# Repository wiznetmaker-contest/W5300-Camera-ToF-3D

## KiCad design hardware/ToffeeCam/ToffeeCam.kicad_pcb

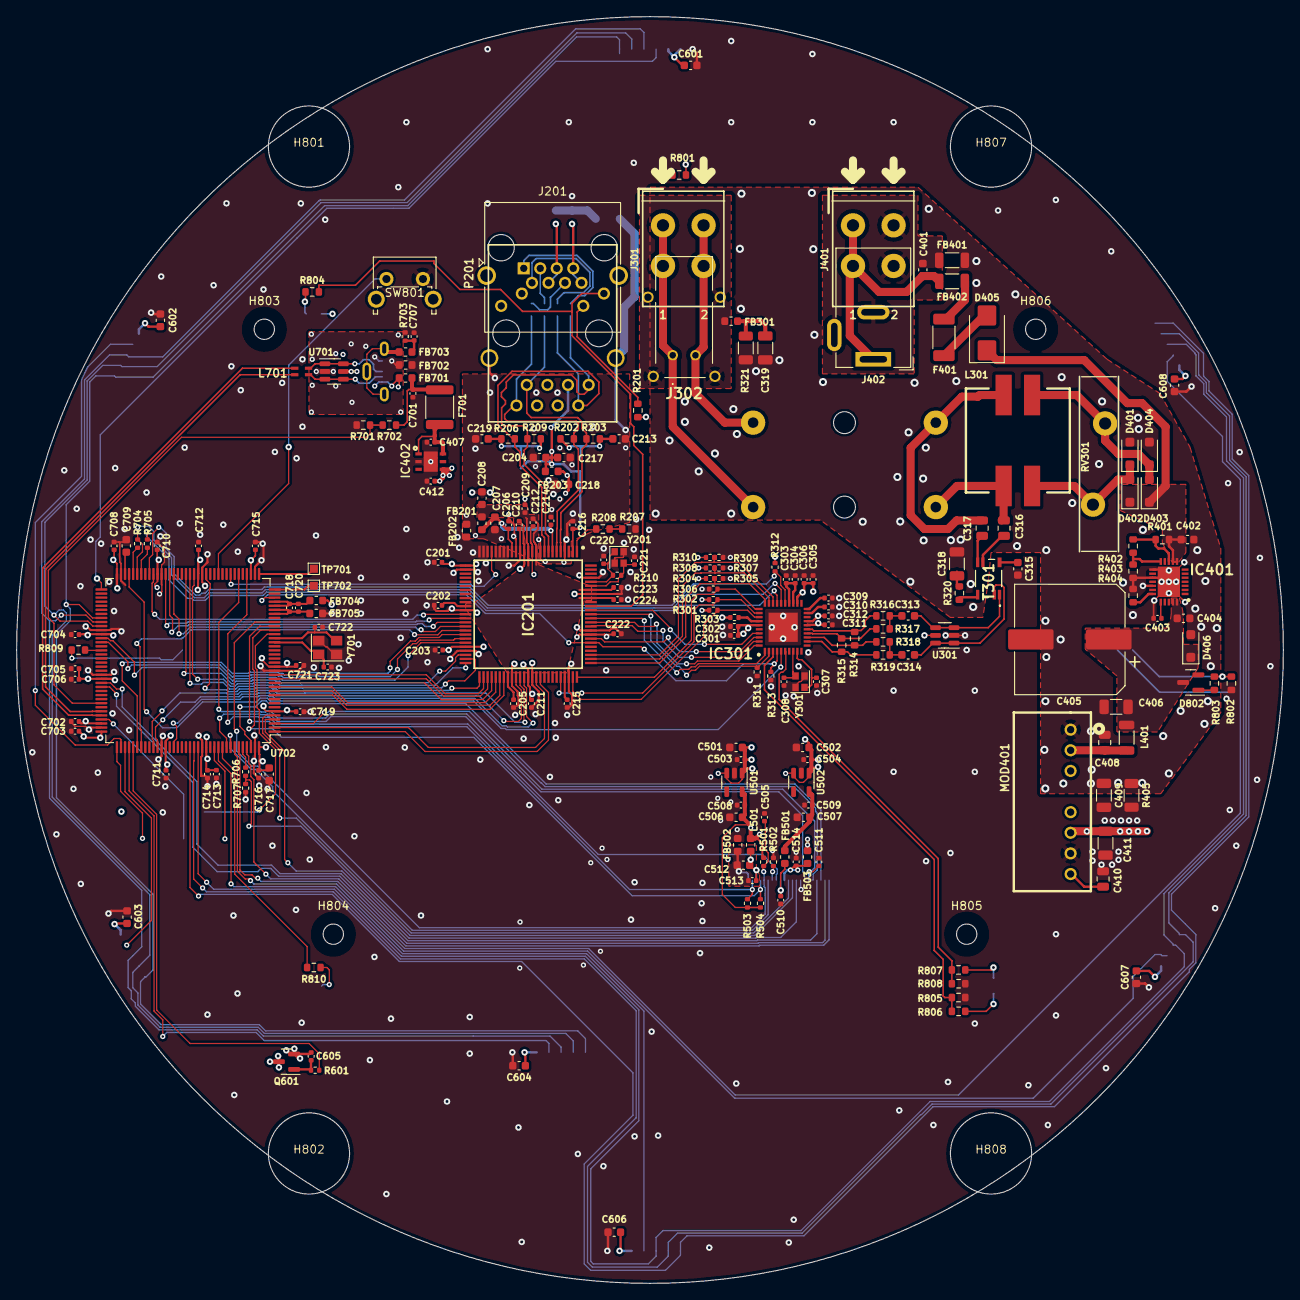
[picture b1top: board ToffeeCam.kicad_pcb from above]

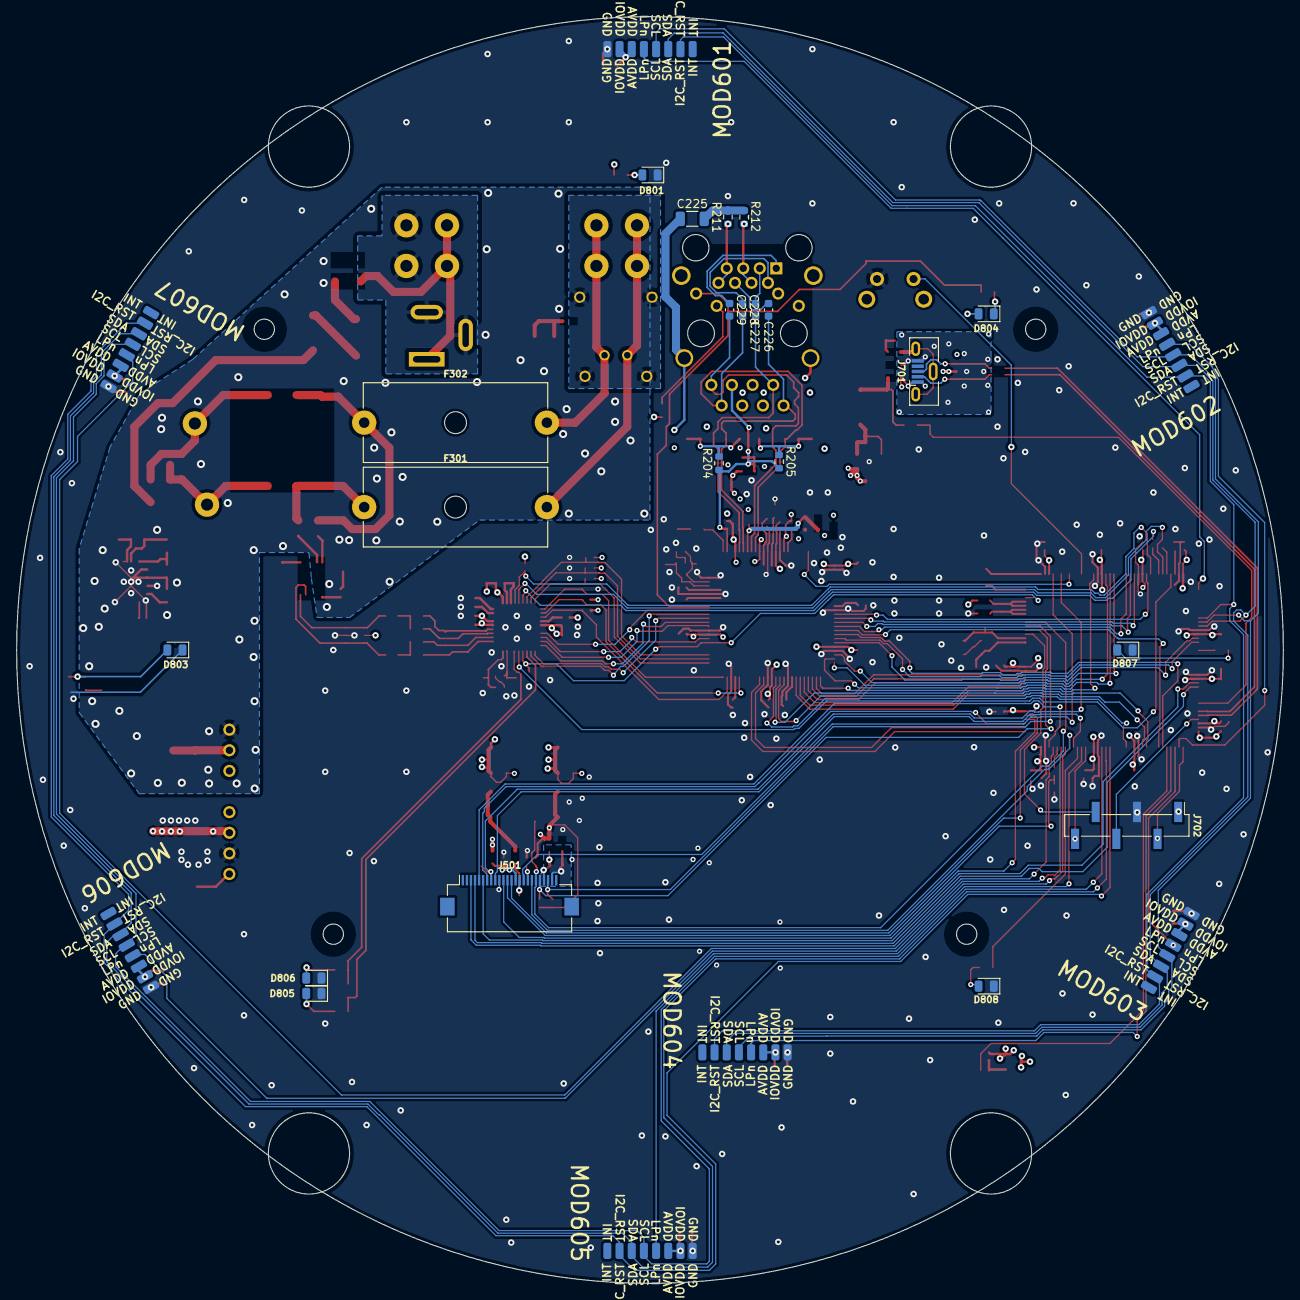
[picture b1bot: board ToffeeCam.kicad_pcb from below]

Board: 4 copper layers, 156.0 x 156.0 mm, 244 parts (28 on the bottom side), 182 nets.

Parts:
C201, C202, C203, C205, C206, C210, C211, C212, C214, C215, C216, C222, C223, C224, C302, C303, C306, C310, C312, C503, C504, C505, C508, C509, C510, C513, C514, C701, C702, C703, C704, C705, C708, C710, C711, C712, C713, C715, C716, C718, C719, C721: 100n; C_0402_1005Metric
C204, C213, C219, C315, C401, C402, C404: 100n; C_0603_1608Metric
C207, C208, C217, C218, C501, C502, C506, C507, C512, C601, C602, C603, C604, C606, C607, C608, C717: 10u; C_0603_1608Metric
C209, C403, C706, C714: 2u2; C_0402_1005Metric
C220, C221: 13p; C_0402_1005Metric
C225, C318, C319, C409: 1n_2kV; C_1206_3216Metric
C226, C227, C228, C229: 33n; C_0603_1608Metric
C301, C305, C311: 10n; C_0402_1005Metric
C304: 680n; C_0402_1005Metric
C307, C308: 16p; C_0402_1005Metric
C309, C407, C412, C605, C720: 1u; C_0402_1005Metric
C313, C314: 220n; C_0603_1608Metric
C316, C317, C408: 1u; C_0805_2012Metric
C405: 330u_50V; CP_Elec_12,5x13.5
C406: 10u; C_1206_3216Metric
C410: 10u; C_0805_2012Metric
C411: 100u; C_1206_3216Metric
C511: 22p; C_0402_1005Metric
C707: 1n; C_0402_1005Metric
C709: 4u7; C_0603_1608Metric
C722, C723: 6p8; C_0402_1005Metric
D401, D402, D403, D404, D406: PMEG6010CEH; D_SOD-123F
D405: SK56; D_SMB
D801, D803, D804, D805, D806, D807, D808: LED; LED_0805_2012Metric
D802: BZX84Cxx; SOT-23
F301, F302: Fuse; Fuseholder_Cylinder-5x20mm_Schurter_0031_8201_Horizontal_Op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
F401: Polyfuse; Fuse_2010_5025Metric
F701: Polyfuse_Small; Fuse_1812_4532Metric
FB201, FB202, FB203, FB301, FB501, FB502, FB503, FB701, FB702, FB703: HH-1M1608-121JT; FB_0603_1608Metric
FB401, FB402: WE-742792122; FB_1206_3216Metric
FB704, FB705: HH-1M1608-221JT; FB_0603_1608Metric
H801, H802, H807, H808: MountingHole; MountingHole-10mm
H803, H804, H805, H806: MountingHole; MountingHole_2.5mm
IC201: W5300; QFP50P1600X1600X160-100N
IC301: ADIN1100BCPZ; ADIN1100
IC401: TPS26400RHFR; QFN50P400X500X100-25N-D
IC402: LDL112PV33R; SON95P300X300X100-7N-D
J201: RJ45; RJ45_Amphenol_RJHSE5380
J301, J401: Messtechnik_AK3001/2-KD-5,0; Messtechnik_AK3001_2-KD-5.0
J302: 09452812800
J402: Wuerth-694108301002; BarrelJack_Wuerth_6941xx301002
J501: Hirose_FH12-24S-0.5SH(55); Hirose_FH12-24S-0.5SH_1x24-1MP_P0.50mm_Horizontal
J701: USB_B_Micro; USB_Micro-B_Molex-105133-0001
J702: Conn_01x06; PinHeader_1x06_P2.54mm_Vertical_SMD_Pin1Left
L301: 100u; 744871101
L401: 470n; L_1206_3216Metric
L501: 3u3; FB_0603_1608Metric
L701: 744233121; WE-CNSW_08059
MOD401: AM3G-2403S-NZ; AM3G-NZ
MOD601, MOD602, MOD603, MOD604, MOD605, MOD606, MOD607: VL53L7CX-SATEL; VL53L5CX-SATEL
P201: RB1-125BAG1A; WIZNET_RB1-125BAG1A
Q601: AO3401A; SOT-23
R201, R207: 330; R_0603_1608Metric
R202, R203, R206, R209, R316, R319: 49R9; R_0603_1608Metric
R204, R205: 0R; R_0603_1608Metric
R208: 12k_1%; R_0603_1608Metric
R210, R703: 1M; R_0402_1005Metric
R211, R212: 75R; R_0603_1608Metric
R301, R302, R303, R304, R305, R306, R307, R308, R309, R310, R311, R313, R503, R504: 4k7; R_0402_1005Metric
R312: 1k5; R_0402_1005Metric
R314, R315: 10k2; R_0603_1608Metric
R317, R318: 5k1; R_0603_1608Metric
R320, R806, R807: 100; R_0603_1608Metric
R321, R405: 1M; R_1206_3216Metric
R401: 237k; R_0603_1608Metric
R402: 6k8; R_0603_1608Metric
R403: 10k; R_0603_1608Metric
R404: 53k6; R_0603_1608Metric
R501, R502, R601: 10k; R_0402_1005Metric
R701: 47k; R_0603_1608Metric
R702: 22k; R_0603_1608Metric
R704, R705: 22R; R_0402_1005Metric
R706: 49R9; R_0402_1005Metric
R707: 330R; R_0402_1005Metric
R801, R804, R809, R810: 330R; R_0603_1608Metric
R802, R803, R805, R808: 4k7; R_0603_1608Metric
RV301: S20K30; RV_Disc_D21.5mm_W4.3mm_P10mm
SW801: SW_Push; SW_Tactile_SPST_Angled_PTS645Vx83-2LFS
T301: 74930000
TP701, TP702: TestPoint; TestPoint_Pad_1.0x1.0mm
U301, U701: WE-TVS-82400102; SOT-23-6
U501: TLV74328PDBVR; SOT-23-5
U502: TLV75512PDBVR; SOT-23-5
U702: STM32U575ZITx; LQFP-144_20x20mm_P0.5mm
Y201, Y301: 7R-25.000MAAQ; Crystal_SMD_2016-4Pin_2.0x1.6mm
Y701: ABM8G-16.000MHZ-4Y-T3; Crystal_SMD_Abracon_ABM8G-4Pin_3.2x2.5mm

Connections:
2V8A: C512.2, C513.2, J501.21, L501.2
2V8D: C506.2, C508.2, FB503.1, L501.1, R501.2, R503.1, R504.1, U501.5 (OUT)
+1V2: C507.2, C509.2, FB501.2, U502.5 (OUT)
+1V8A: C206.2, C207.1, C214.2, FB201.2, IC201.7 (VCC1A8_1), IC201.17 (VCC1A8_2)
+1V8D: C202.2, C205.1, C208.1, C209.1, C212.2, C215.1, C223.1, C224.1, FB201.1, IC201.11 (VCC1V8_1), IC201.13 (1V8O), IC201.36 (VCC1V8_2), IC201.58 (VCC1V8_3), IC201.72 (VCC1V8_4), IC201.92 (VCC1V8_5), IC201.94 (VCC1V8_6)
+3.3VP: C601.1, C602.1, C603.1, C604.1, C606.1, C607.1, C608.1, MOD601.6 (AVDD), MOD601.7 (IOVDD), MOD602.6 (AVDD), MOD602.7 (IOVDD), MOD603.6 (AVDD), MOD603.7 (IOVDD), MOD604.6 (AVDD), MOD604.7 (IOVDD), MOD605.6 (AVDD), MOD605.7 (IOVDD), MOD606.6 (AVDD), MOD606.7 (IOVDD), MOD607.6 (AVDD), MOD607.7 (IOVDD), Q601.3 (D)
+3V3: C201.2, C203.2, C210.2, C211.1, C218.1, C222.1, C301.1, C302.2, C305.1, C306.1, C311.1, C312.1, C411.1, C412.1, C501.2, C502.2, C503.2, C504.2, C605.2, C702.2, C703.2, C704.2, C705.2, C706.2, C708.2, C710.2, C711.2, C712.2, C713.2, C714.2, C715.2, C716.2, C717.2, C719.2, C721.2, D804.2 (A), FB203.1, FB704.2, IC201.14 (VCC3V3_1), IC201.26 (VCC3V3_2), IC201.46 (VCC3V3_3), IC201.63 (VCC3V3_4), IC201.83 (VCC3V3_5), IC301.16 (AVDD_H_1), IC301.17 (AVDD_H_2), IC301.22 (AVDD_L), IC301.35 (VDDIO), IC402.4 (VOUT), J702.1, MOD401.6 (+Vout), Q601.2 (S), R201.2, R301.1, R302.1, R303.1, R304.1, R308.1, R310.1, R312.2, R801.2, U301.5, U501.1 (IN), U501.3 (EN), U502.1 (IN), U502.3 (EN), U702.6 (VBAT), U702.17 (VDD), U702.39 (VDD), U702.52 (VDD), U702.62 (VDD), U702.72 (VDD), U702.84 (VDD), U702.95 (VDDIO2), U702.106 (VDDUSB), U702.108 (VDD), U702.121 (VDD), U702.131 (VDDIO2), U702.144 (VDD)
+3V3A: C204.1, C216.2, C217.1, FB203.2, IC201.2 (VCC3A3), P201.R3 (CT), R204.1, R205.2
+5V-USB: C407.1, F701.2, IC402.1 (EN), IC402.6 (VIN)
/Camera/CAM-PWDN: J501.17, R502.2
/MCU/CAMXCLK: R706.2, U702.140 (PB9)
/MCU/SWCLK: J702.2, U702.109 (PA14)
/MCU/SWDIO: J702.4, U702.105 (PA13)
/MCU/SWO: J702.6, U702.133 (PB3)
/MCU/USB-5V: FB701.1, J701.1 (VBUS), U701.5
/MCU/USB-DN: L701.2, U702.103 (PA11)
/MCU/USB-DP: L701.3 (4), U702.104 (PA12)
/MCU/USB-GND: FB702.2, J701.5 (GND), U701.2
/MCU/USB-VBUS-DETECT: R701.1, R702.2, U702.101 (PA9)
/MCU/VBUS: C701.1, F701.1, FB701.2, R702.1
/MCU/nRST: J702.5, U702.25 (NRST)
/PowerSupply/CONV_IN: C408.1, L401.2, MOD401.2 (+Vin)
/PowerSupply/PROTECT-IN: C402.1, D402.1 (K), D403.1 (K), D405.1 (K), IC401.8 (IN), R401.1
/PowerSupply/SUPP_M: C401.2, FB401.1, J401.2, J402.2, J402.3
/PowerSupply/SUPP_P: C401.1, FB402.2, J401.1, J402.1
/Wiznet-W5300/RXIN: C226.2, IC201.6 (RXIN), P201.R8 (RD-), R202.1
/Wiznet-W5300/RXIP: C227.2, IC201.5 (RXIP), P201.R7 (RD+), R203.1
/Wiznet-W5300/TXON: C228.2, IC201.9 (TXON), P201.R2 (TD-), R206.2
/Wiznet-W5300/TXOP: C229.2, IC201.8 (TXOP), P201.R1 (TD+), R209.2
CAM-D0: J501.6, U702.96 (PC6)
CAM-D1: J501.4, U702.97 (PC7)
CAM-D2: J501.3, U702.141 (PE0)
CAM-D3: J501.5, U702.142 (PE1)
CAM-D4: J501.7, U702.3 (PE4)
CAM-D5: J501.9, U702.136 (PB6)
CAM-D6: J501.11, U702.4 (PE5)
CAM-D7: J501.13, U702.5 (PE6)
CAM-HSYNC: J501.16, U702.40 (PA4)
CAM-PCLK: C511.2, J501.8, U702.42 (PA6)
CAM-SCL: J501.20, R504.2, U702.26 (PC0)
CAM-SDA: J501.22, R503.2, U702.27 (PC1)
CAM-VSYNC: J501.18, U702.137 (PB7)
CAM-XCLK: J501.12, R706.1, R707.1
CAM-nRESET: C505.1, J501.19, R501.1, U702.28 (PC2)
CAMGNDA: C512.1, C513.1, FB502.1, J501.23
ETH-BUS-ADDR0: IC201.57 (ADDR0), U702.10 (PF0)
ETH-BUS-ADDR1: IC201.56 (ADDR1), U702.11 (PF1)
ETH-BUS-ADDR2: IC201.55 (ADDR2), U702.12 (PF2)
ETH-BUS-ADDR3: IC201.54 (ADDR3), U702.13 (PF3)
ETH-BUS-ADDR4: IC201.53 (ADDR4), U702.14 (PF4)
ETH-BUS-ADDR5: IC201.52 (ADDR5), U702.15 (PF5)
ETH-BUS-ADDR6: IC201.51 (ADDR6), U702.50 (PF12)
ETH-BUS-ADDR7: IC201.50 (ADDR7), U702.53 (PF13)
ETH-BUS-ADDR8: IC201.49 (ADDR8), U702.54 (PF14)
ETH-BUS-ADDR9: IC201.48 (ADDR9), U702.55 (PF15)
ETH-BUS-DATA0: IC201.45 (DATA0), U702.85 (PD14)
ETH-BUS-DATA1: IC201.44 (DATA1), U702.86 (PD15)
ETH-BUS-DATA2: IC201.43 (DATA2), U702.114 (PD0)
ETH-BUS-DATA3: IC201.42 (DATA3), U702.115 (PD1)
ETH-BUS-DATA4: IC201.41 (DATA4), U702.58 (PE7)
ETH-BUS-DATA5: IC201.40 (DATA5), U702.59 (PE8)
ETH-BUS-DATA6: IC201.39 (DATA6), U702.60 (PE9)
ETH-BUS-DATA7: IC201.38 (DATA7), U702.63 (PE10)
ETH-BUS-nCS: IC201.62 (/CS), U702.123 (PD7)
ETH-BUS-nINT: IC201.65 (/INT), U702.2 (PE3)
ETH-BUS-nRD: IC201.61 (/RD), U702.118 (PD4)
ETH-BUS-nRESET: IC201.66 (/RESET), U702.1 (PE2)
ETH-BUS-nWR: IC201.60 (/WR), U702.119 (PD5)
ETH-LINKLED: IC201.90 (LINKLED), P201.L4, R804.2
ETH-MEDIA_SEL: IC201.22 (TEST_MODE0), U702.44 (PC4)
ETHGNDA: C204.2, C206.1, C207.2, C213.2, C214.1, C216.1, C217.2, C219.2, C225.1, FB202.2, IC201.4 (GNDA_1), IC201.10 (GNDA_2), IC201.16 (GNDA_3), P201.S1, P201.S2
GND: C201.1, C202.1, C203.1, C205.2, C208.2, C209.2, C210.1, C211.2, C212.1, C215.2, C218.2, C220.2, C221.1, C222.2, C223.2, C224.2, C301.2, C302.1, C303.2, C304.2, C305.2, C306.2, C307.2, C308.1, C309.2, C310.2, C311.2, C312.2, C315.1, C407.2, C409.2, C410.2, C411.2, C412.2, C501.1, C502.1, C503.1, C504.1, C505.2, C506.1, C507.1, C508.1, C509.1, C510.1, C511.1, C514.2, C601.2, C602.2, C603.2, C604.2, C606.2, C607.2, C608.2, C701.2, C702.1, C703.1, C704.1, C705.1, C706.1, C707.2, C708.1, C709.1, C710.1, C711.1, C712.1, C713.1, C714.1, C715.1, C716.1, C717.1, C719.1, C721.1, C722.2, C723.1, D801.1 (K), D803.1 (K), D805.1 (K), D806.1 (K), D807.1 (K), D808.1 (K), FB202.1, FB502.2, FB702.1, FB705.2, IC201.12 (GND_1), IC201.15 (GND_2), IC201.18 (BIT16EN), IC201.19 (TEST_MODE3), IC201.20 (TEST_MODE2), IC201.21 (TEST_MODE1), IC201.23 (OP_MODE0_1), IC201.24 (OP_MODE0_2), IC201.25 (OP_MODE2), IC201.27 (GND_3), IC201.37 (GND_4), IC201.47 (GND_5), IC201.59 (GND_6), IC201.64 (GND_7), IC201.73 (GND_8), IC201.84 (GND_9), IC201.93 (GND_10), IC201.97 (GND_11), IC301.41 (GND), IC402.2 (GND), IC402.7 (EP), J501.10, J702.3, MOD401.7 (-Vout), MOD601.8 (GND), MOD602.8 (GND), MOD603.8 (GND), MOD604.8 (GND), MOD605.8 (GND), MOD606.8 (GND), MOD607.8 (GND), R207.1, R305.1, R306.1, R307.1, R309.1, R311.1, R313.1, R405.2, R502.1, R701.2, R703.2, R707.2, R802.1, R805.2, R808.2, SW801.2, U301.2, U501.2 (GND), U502.2 (GND), U702.16 (VSS), U702.38 (VSS), U702.51 (VSS), U702.61 (VSS), U702.71 (VSS), U702.83 (VSS), U702.94 (VSS), U702.107 (VSS), U702.120 (VSS), U702.130 (VSS), U702.143 (VSS), Y201.2, Y201.4, Y301.2, Y301.4, Y701.2, Y701.4
GNDPWR: C318.2, C319.2, C402.2, C403.2, C404.2, C405.2, C406.2, C408.2, C409.1, D401.2 (A), D404.2 (A), D406.2 (A), FB401.2, IC401.13 (MODE), IC401.15 (RTN), IC401.17 (GND), IC401.25 (EP), MOD401.1 (-Vin), R321.2, R403.2, R404.2, R405.1
MCU-STATUS-1: R809.2, U702.88 (PG3)
MCU-STATUS-2: R810.2, U702.135 (PB5)
MII-CRS: IC201.81 (MII_CRS), IC301.4 (LINK_ST/PHYAD_2), R313.2, U702.34 (PA0)
MII-RXCLK: IC201.71 (MII_RXC), IC301.32 (MACIF_SEL0/RX_CLK), R302.2
MII-RXD0: IC201.75 (MII_RXD0), IC301.31 (~TX2P4_EN/RXD_0), R306.2
MII-RXD1: IC201.76 (MII_RXD1), IC301.30 (MS_SEL/RXD_1), R304.2, R305.2
MII-RXD2: IC201.77 (MII_RXD2), IC301.29 (PHYAD_0/RXD_2), R307.2, R308.2
MII-RXD3: IC201.78 (MII_RXD3), IC301.28 (PHYAD_1/RXD_3), R309.2, R310.2
MII-RXDV: IC201.74 (MII_RXDV), IC301.33 (~SWPD_EN/RX_DV), R301.2
MII-TXCLK: IC201.82 (MII_TXC), IC301.38 (TX_CLK)
MII-TXD0: IC201.85 (/SPDLED(MII_TXD0)), IC301.39 (TXD_0)
MII-TXD1: IC201.86 (/FDXLED(MII_TXD1)), IC301.40 (TXD_1)
MII-TXD2: IC201.87 (/COLLED(MLL_TXD2)), IC301.1 (TXD_2)
MII-TXD3: IC201.88 (/RXLED(MII_TXD3)), IC301.2 (TXD_3/MEDIA_CNV), R311.2
MII-TXEN: IC201.89 (/TXLED(MII_TXEN)), IC301.37 (TX_EN)
unnamed: C213.1, R202.2, R203.2, R204.2
unnamed: C219.1, R205.1, R206.1, R209.1
unnamed: C225.2, R211.2, R212.2
unnamed: C226.1, J201.6
unnamed: C227.1, J201.3
unnamed: C228.1, J201.2
unnamed: C229.1, J201.1
unnamed: C313.2, R316.2, R317.2
unnamed: C314.1, R318.2, R319.2
unnamed: C316.2, F301.1, L301.4
unnamed: C317.2, F302.1, L301.1
unnamed: C318.1, R320.2
unnamed: C319.1, FB301.2, R321.1
unnamed: C707.1, FB703.2, R703.1
unnamed: D405.2 (A), F401.2
unnamed: D801.2 (A), R801.1
unnamed: D802.1 (A), R803.2
unnamed: D803.2 (A), R802.2, R803.1
unnamed: D804.1 (K), R804.1
unnamed: D805.2 (A), R806.2
unnamed: D806.2 (A), R807.2
unnamed: D807.2 (A), R809.1
unnamed: D808.2 (A), R810.1
unnamed: F401.1, FB402.1
unnamed: FB301.1, J302.MH1, J302.MH2, J302.MH3, J302.MH4
unnamed: IC201.1 (RSET_BG), R208.2
unnamed: C221.2, IC201.95 (XTLN), R210.1, Y201.3
unnamed: C220.1, IC201.96 (XTLP), R210.2, Y201.1
unnamed: C310.1, IC301.19 (CEXT_2)
unnamed: C309.1, IC301.20 (CEXT_3)
unnamed: C303.1, C304.1, IC301.23 (DLDO_1P1), IC301.24 (DVDD_1P1)
unnamed: IC301.34 (MAC_IFSEL1/RX_ER), R303.2
unnamed: IC301.13 (RXN), R314.2, R318.1
unnamed: IC301.14 (RXP), R315.1, R317.1
unnamed: IC301.12 (TXN), R315.2, R319.1
unnamed: IC301.15 (TXP), R314.1, R316.1
unnamed: C308.2, IC301.8 (XTAL_I/CLK_IN), Y301.3
unnamed: C307.1, IC301.9 (XTAL_O), Y301.1
unnamed: C403.1, IC401.20 (DVDT)
unnamed: IC401.19 (ILIM), R404.1
unnamed: IC401.12 (OVP), R402.2, R403.1
unnamed: IC401.10 (UVLO), R401.2, R402.1
unnamed: J201.4, J201.5, R212.1
unnamed: J201.7, J201.8, R211.1
unnamed: F301.2, J301.1, J302.1 (BI_DA+)
unnamed: F302.2, J301.2, J302.2 (BI_DA-)
unnamed: C514.1, FB503.2, J501.14
unnamed: C510.2, FB501.1, J501.15
unnamed: J701.3 (D+), L701.4 (3), U701.1, U701.6
unnamed: J701.2 (D-), L701.1, U701.3, U701.4
unnamed: FB703.1, J701.6 (Shield)
unnamed: C410.1, MOD401.8 (Cs)
unnamed: P201.L3, R201.1
unnamed: C605.1, Q601.1 (G), R601.2
unnamed: R207.2, R208.1
unnamed: C313.1, T301.1 (N1), U301.3, U301.4
unnamed: C315.2, T301.5 (N1/N4)
unnamed: R320.1, T301.3 (N3_1), T301.4 (N2_1)
unnamed: C316.1, T301.6 (N2_2)
unnamed: C317.1, T301.7 (N3_2)
unnamed: C314.2, T301.2 (N4), U301.1, U301.6
unnamed: TP702.1, U702.36 (PA2)
unnamed: TP701.1, U702.37 (PA3)
unnamed: R705.1, U702.66 (PE13)
unnamed: R704.1, U702.68 (PE15)
unnamed: C723.2, U702.23 (PH0), Y701.1
unnamed: C722.1, U702.24 (PH1), Y701.3
unnamed: C709.2, U702.70 (VCAP)
unnamed: C718.2, C720.2, FB704.1, U702.32 (VREF+), U702.33 (VDDA)
unnamed: C718.1, C720.1, FB705.1, U702.30 (VSSA), U702.31 (VREF-)
PUSHBUTTON: SW801.1, U702.47 (PB1)
PWR_HV: C404.1, C405.1, C406.1, D406.1 (K), D802.3 (K), IC401.23 (OUT), L401.1
SPE-LED-0: IC301.3 (LED_0), R805.1, R806.1
SPE-LED-1: IC301.6 (LED_1), R807.1, R808.1
SPE-MDC: IC301.27 (MDC), R705.2
SPE-MDIO: IC301.26 (MDIO), R704.2, U702.67 (PE14)
SPE-nINT: IC301.25 (~INT), R312.1, U702.64 (PE11)
SPE-nRESET: IC301.5 (~RESET), U702.69 (PB10)
SPoE-1: D401.1 (K), D402.2 (A), L301.3, RV301.2
SPoE-2: D403.2 (A), D404.1 (K), L301.2, RV301.1
ToF-1-LPn: MOD601.5 (LPn), U702.73 (PB12)
ToF-2-LPn: MOD602.5 (LPn), U702.110 (PA15)
ToF-3-LPn: MOD603.5 (LPn), U702.111 (PC10)
ToF-4-LPn: MOD604.5 (LPn), U702.112 (PC11)
ToF-5-LPn: MOD605.5 (LPn), U702.134 (PB4)
ToF-6-LPn: MOD606.5 (LPn), U702.138 (PH3)
ToF-7-LPn: MOD607.5 (LPn), U702.139 (PB8)
ToF-I2C-1-RST: MOD601.2 (I2C_RST), MOD602.2 (I2C_RST), MOD603.2 (I2C_RST), MOD604.2 (I2C_RST), U702.80 (PD11)
ToF-I2C-1-SCL: MOD601.4 (SCL), MOD602.4 (SCL), MOD603.4 (SCL), MOD604.4 (SCL), U702.81 (PD12)
ToF-I2C-1-SDA: MOD601.3 (SDA), MOD602.3 (SDA), MOD603.3 (SDA), MOD604.3 (SDA), U702.82 (PD13)
ToF-I2C-2-RST: MOD605.2 (I2C_RST), MOD606.2 (I2C_RST), MOD607.2 (I2C_RST), U702.127 (PG12)
ToF-I2C-2-SCL: MOD605.4 (SCL), MOD606.4 (SCL), MOD607.4 (SCL), U702.129 (PG14)
ToF-I2C-2-SDA: MOD605.3 (SDA), MOD606.3 (SDA), MOD607.3 (SDA), U702.128 (PG13)
ToF-nPWDN: R601.1, U702.113 (PC12)

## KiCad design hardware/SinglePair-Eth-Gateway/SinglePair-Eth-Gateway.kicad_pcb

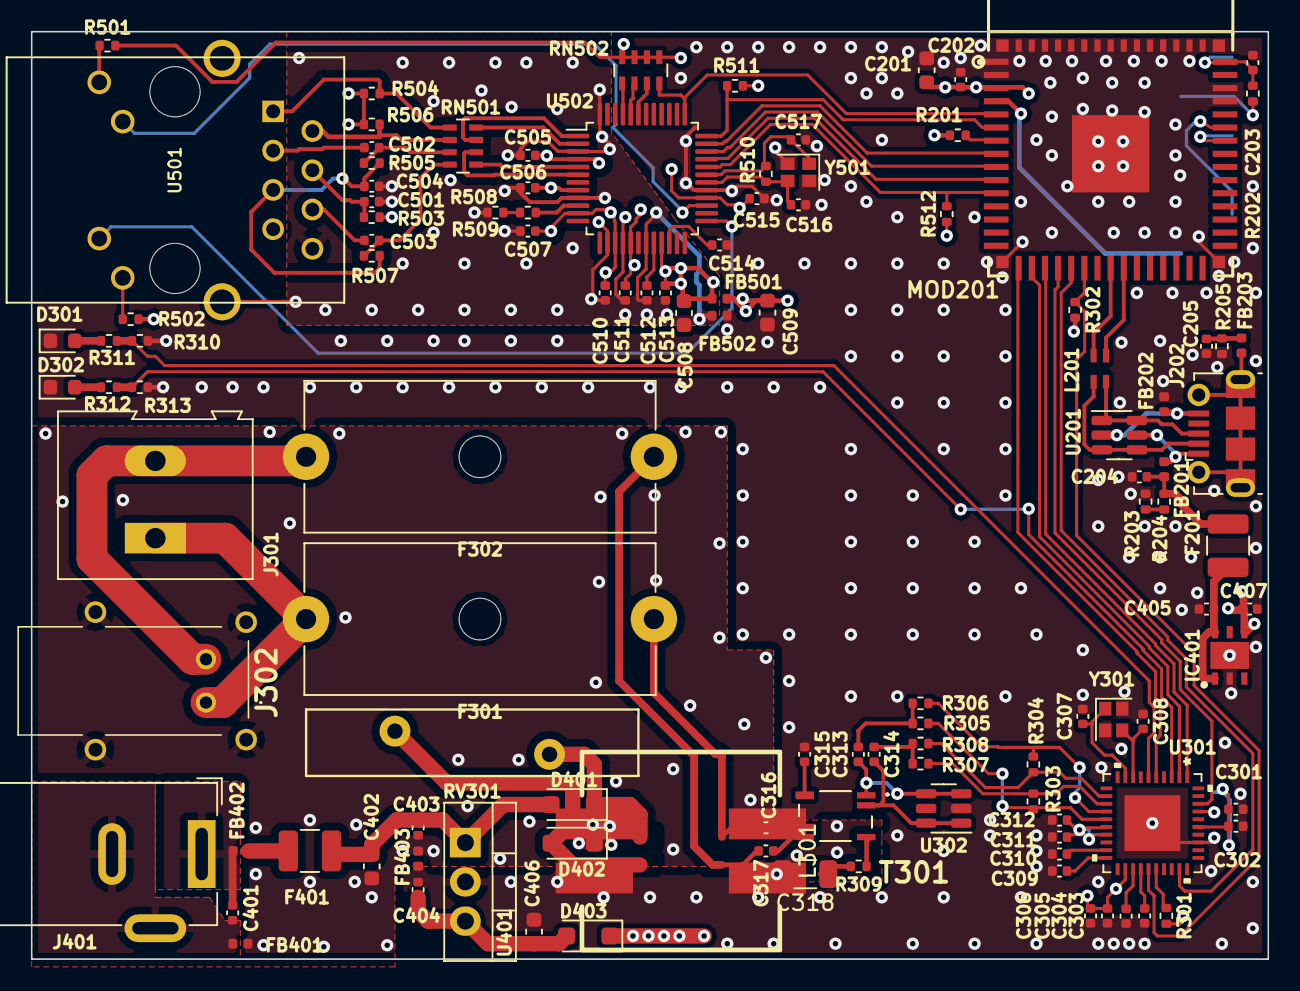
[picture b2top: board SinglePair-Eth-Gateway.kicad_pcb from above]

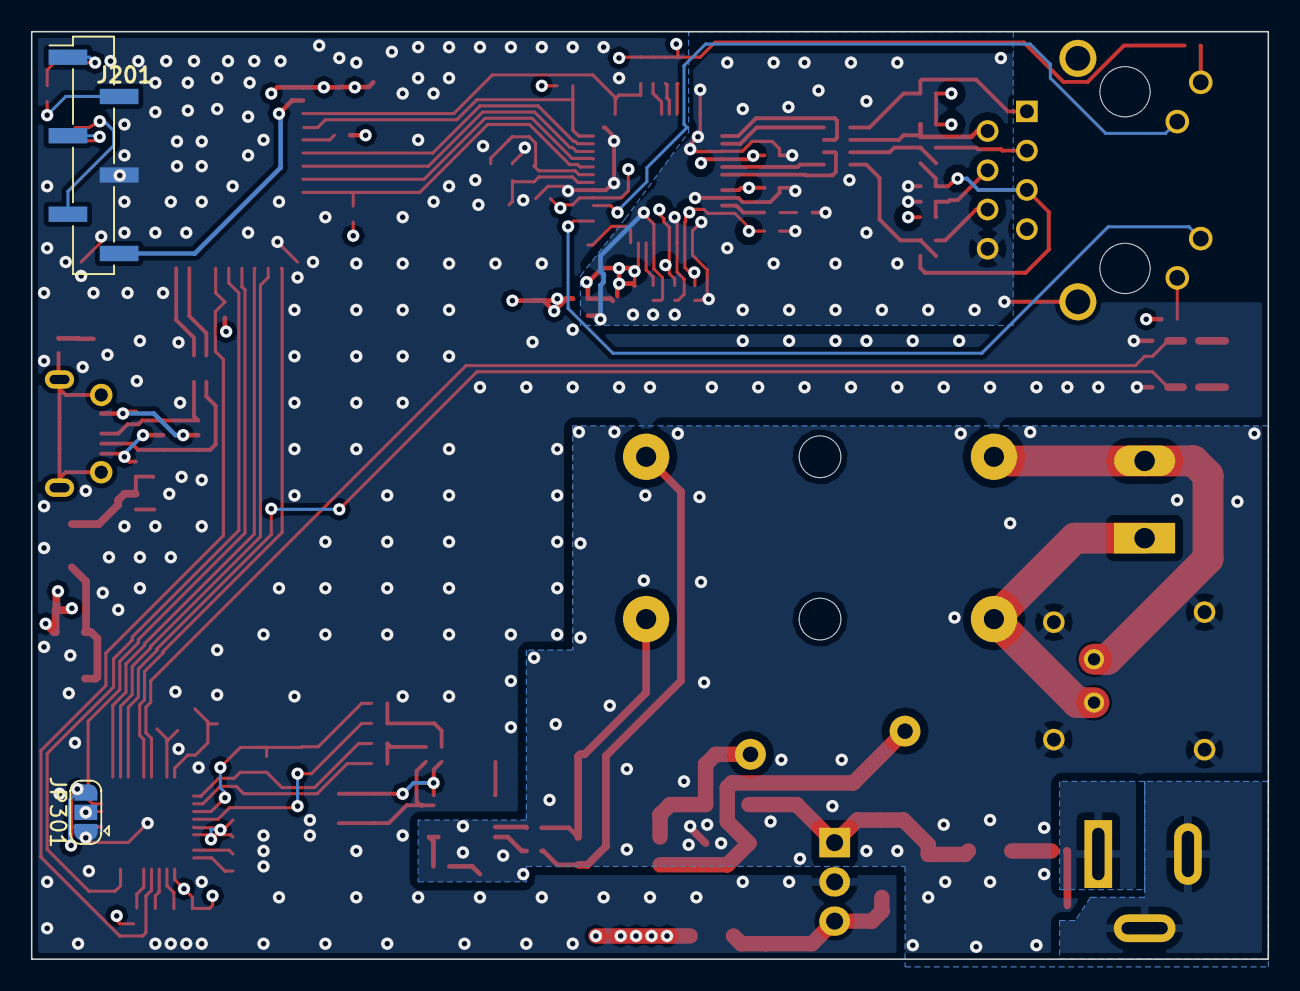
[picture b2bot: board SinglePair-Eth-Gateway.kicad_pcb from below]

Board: 4 copper layers, 80.0 x 60.0 mm, 116 parts (2 on the bottom side), 94 nets.

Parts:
C201, C402, C406, C508, C509: 10u; C_0603_1608Metric
C202, C204, C301, C303, C306, C310, C312, C315, C401, C403, C404, C505, C506, C507, C510, C511, C513, C514, C515: 100n; C_0402_1005Metric
C203, C309, C316, C317, C405, C407: 1u; C_0402_1005Metric
C205: 4n7; C_0402_1005Metric
C302, C305, C311, C504: 10n; C_0402_1005Metric
C304: 680n; C_0402_1005Metric
C307, C308, C516, C517: 13p; C_0402_1005Metric
C313, C314: 220n; C_0402_1005Metric
C318: 1n; C_1206_3216Metric
C501: 22n; C_0402_1005Metric
C502, C503: 6n8; C_0402_1005Metric
C512: 4u7; C_0402_1005Metric
D301, D302: LED; LED_0603_1608Metric
D401, D402, D403: PMEG6010CEH; D_SOD-123F
F201: Polyfuse_Small; Fuse_1210_3225Metric
F301, F302: Fuse; Fuseholder_Cylinder-5x20mm_Schurter_0031_8201_Horizontal_Op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
F401: Polyfuse; Fuse_1210_3225Metric
FB201, FB202, FB203, FB401, FB402, FB403, FB501, FB502: HH-1M1005-221JT; L_0402_1005Metric
IC401: LDL112PV33R; SON95P300X300X100-7N-D
J201: Conn_01x06_Pin; PinHeader_1x06_P2.54mm_Vertical_SMD_Pin1Left
J202: USB_B_Micro; USB_Micro-B_Molex-105017-0001
J301: Screw_Terminal_01x02; TerminalBlock_Altech_AK300-2_P5.00mm
J302: 09452812800
J401: Wuerth-694108301002; BarrelJack_Wuerth_6941xx301002
JP301: SolderJumper_3_Open; SolderJumper-3_P1.3mm_Open_RoundedPad1.0x1.5mm
L201: 744233121; WE-CNSW_08059
L301: 100u; 744871101
MOD201: ESP32-S3-MINI-1-N8; XCVR_ESP32-S3-MINI-1-N8
R201, R202, R511, R512: 10k; R_0402_1005Metric
R203: 47k; R_0402_1005Metric
R204: 22k; R_0402_1005Metric
R205, R510: 1M; R_0402_1005Metric
R301, R302: 1k5; R_0402_1005Metric
R303, R304: 10R2; R_0402_1005Metric
R305, R308, R504, R505, R506, R507: 49R9; R_0402_1005Metric
R306, R307: 5R1; R_0402_1005Metric
R309, R311, R312: 100R; R_0402_1005Metric
R310, R313: 4k7; R_0402_1005Metric
R501, R502: 330R; R_0402_1005Metric
R503: 10R; R_0402_1005Metric
R508: 300; R_0402_1005Metric
R509: 12k_1%; R_0402_1005Metric
RN501: 33R; R_Array_Concave_4x0603
RN502: 10k; R_Array_Concave_4x0603
RV301: S20K30; RV_Disc_D21.5mm_W4.3mm_P10mm
T301: 74930000
U201, U302: WE-TVS-82400102; SOT-23-6
U301: ADIN1110BCPZ; ADIN1110
U401: VXO7803-1000; TO-220-3_Vertical
U501: 7499010211A
U502: W5500; LQFP-48_7x7mm_P0.5mm
Y301, Y501: 830108212509; Crystal_SMD_2016-4Pin_2.0x1.6mm

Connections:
+3V3: C201.2, C202.2, C301.1, C302.1, C305.1, C306.1, C311.1, C312.1, C407.1, C509.1, C515.1, D403.1 (K), FB501.1, IC401.4 (VOUT), J201.2, JP301.3 (B), MOD201.3 (3V3), R201.1, R202.1, R301.2, R302.2, R501.2, R502.2, R511.2, R512.1, RN502.5 (R4.2), RN502.6 (R3.2), RN502.7 (R2.2), RN502.8 (R1.2), U301.16 (AVDD_H), U301.17 (AVDD_H), U301.22 (AVDD_L), U301.35 (VDDIO), U502.28 (VDD)
+3V3A: C505.2, C506.2, C507.2, C508.1, C510.2, C511.2, C513.2, FB501.2, R503.2, R504.1, R506.1, U502.4 (AVDD), U502.8 (AVDD), U502.11 (AVDD), U502.15 (AVDD), U502.17 (AVDD), U502.21 (AVDD)
+5V-USB: C405.1, F201.2, IC401.1 (EN), IC401.6 (VIN)
+24V: C402.1, C403.1, D401.2 (A), F401.2, U401.1 (IN)
/ADIN1110/LED-0: R312.1, R313.1, U301.3 (LED_0)
/ADIN1110/LED-1: R310.1, R311.1, U301.6 (LED_1)
/ESP32-S3/BOOT: J201.6, MOD201.4 (IO0)
/ESP32-S3/EN: C203.1, J201.1, MOD201.45 (EN), R202.2
/ESP32-S3/RXD0: J201.5, MOD201.40 (RXD0)
/ESP32-S3/TXD0: J201.3, MOD201.39 (TXD0)
/ESP32-S3/USB-5V: FB201.1, J202.1 (VBUS), U201.5
/ESP32-S3/USB-DM: L201.2, MOD201.23 (IO19)
/ESP32-S3/USB-DP: L201.3 (4), MOD201.24 (IO20)
/ESP32-S3/USB-GND: FB202.2, J202.5 (GND), U201.2
/ESP32-S3/USB-VBUS: R203.1, R204.2
/ESP32-S3/VBUS: C204.1, F201.1, FB201.2, R204.1
/PowerSupply/GND-HV: C401.2, FB401.1, J401.2, J401.3
/PowerSupply/PWR-HV: C401.1, FB402.2, J401.1
/Wiznet-W5500/ACTLED: U501.10 (D2), U502.27 (ACTLED)
/Wiznet-W5500/LINKLED: U501.11 (D4), U502.25 (LINKLED)
/Wiznet-W5500/RXIN: RN501.1 (R1.1), U502.5 (RXN)
/Wiznet-W5500/RXIP: RN501.2 (R2.1), U502.6 (RXP)
/Wiznet-W5500/RXN: C503.2, R507.1, RN501.8 (R1.2)
/Wiznet-W5500/RXP: C502.2, R505.1, RN501.7 (R2.2)
/Wiznet-W5500/TXN: R506.2, RN501.6 (R3.2), U501.2 (TD-)
/Wiznet-W5500/TXON: RN501.3 (R3.1), U502.1 (TXN)
/Wiznet-W5500/TXOP: RN501.4 (R4.1), U502.2 (TXP)
/Wiznet-W5500/TXP: R504.2, RN501.5 (R4.2), U501.1 (TD+)
ETH-MISO: MOD201.9 (IO5), U502.34 (MISO)
ETH-MOSI: MOD201.8 (IO4), U502.35 (MOSI)
ETH-SCK: MOD201.10 (IO6), U502.33 (SCLK)
ETH-nCS: MOD201.11 (IO7), R512.2, U502.32 (~SCS)
ETH-nINT: MOD201.6 (IO2), R511.1, U502.36 (~INT)
ETH-nRST: MOD201.5 (IO1), RN502.4 (R4.1), U502.37 (~RST)
ETHGNDA: C501.2, C504.2, C505.1, C506.1, C507.1, C508.2, C510.1, C511.1, C512.2, C513.1, FB502.2, R508.1, U501.8 (C1), U501.CASE@1, U501.CASE@2, U502.3 (AGND), U502.9 (AGND), U502.14 (AGND), U502.16 (AGND), U502.19 (AGND), U502.48 (AGND)
GND: C201.1, C202.1, C203.2, C204.2, C205.2, C301.2, C302.2, C303.2, C304.2, C305.2, C306.2, C307.2, C308.1, C309.2, C310.2, C311.2, C312.2, C315.1, C404.2, C405.2, C406.2, C407.2, C509.2, C514.2, C515.2, C516.1, C517.2, D301.1 (K), D302.1 (K), FB202.1, FB403.1, FB502.1, IC401.2 (GND), IC401.7 (EP), J201.4, JP301.1 (A), MOD201.GND, R203.2, R205.2, R310.2, R313.2, U301.33 (SWPD_ENB), U301.41 (EPAD), U302.2, U401.2 (GND), U502.29 (GND), Y301.2, Y301.4, Y501.2, Y501.4
GNDPWR: C318.2, C402.2, C403.2, D402.1 (K), FB401.2, FB403.2, J302.MH1, J302.MH2, J302.MH3, J302.MH4
unnamed: C205.1, FB203.2, R205.1
unnamed: C313.2, R305.2, R306.2
unnamed: C314.1, R307.2, R308.2
unnamed: C316.1, F301.1, L301.2
unnamed: C317.2, F302.1, L301.3
unnamed: C318.1, R309.2
unnamed: D301.2 (A), R311.2
unnamed: D302.2 (A), R312.2
unnamed: C404.1, C406.1, D403.2 (A), U401.3 (OUT)
unnamed: F401.1, FB402.1
unnamed: J202.3 (D+), L201.4 (3), U201.1, U201.6
unnamed: J202.2 (D-), L201.1, U201.3, U201.4
unnamed: FB203.1, J202.6 (Shield)
unnamed: F301.2, J301.1, J302.1 (BI_DA+)
unnamed: F302.2, J301.2, J302.2 (BI_DA-)
unnamed: JP301.2 (C), U301.37 (SPI_CFG1)
unnamed: MOD201.7 (IO3), R201.2
unnamed: R508.2, R509.1
unnamed: RN502.1 (R1.1), U502.45 (PMODE0)
unnamed: RN502.2 (R2.1), U502.44 (PMODE1)
unnamed: RN502.3 (R3.1), U502.43 (PMODE2)
unnamed: C313.1, T301.1 (N1), U302.3, U302.4
unnamed: C315.2, T301.5 (N1/N4)
unnamed: R309.1, T301.3 (N3_1), T301.4 (N2_1)
unnamed: C316.2, T301.6 (N2_2)
unnamed: C317.1, T301.7 (N3_2)
unnamed: C314.2, T301.2 (N4), U302.1, U302.6
unnamed: C310.1, U301.19 (CEXT_2)
unnamed: C309.1, U301.20 (CEXT_3)
unnamed: C304.1, U301.23 (DLDO_1P1)
unnamed: C303.1, U301.24 (DVDD_1P1)
unnamed: R303.2, R307.1, U301.13 (RXN)
unnamed: R304.1, R306.1, U301.14 (RXP)
unnamed: R301.1, U301.26 (TEST1)
unnamed: R304.2, R308.1, U301.12 (TXN)
unnamed: R303.1, R305.1, U301.15 (TXP)
unnamed: C308.2, U301.8 (XTAL_I/CLK_IN), Y301.3
unnamed: C307.1, U301.9 (XTAL_O), Y301.1
unnamed: R501.1, U501.9 (D1)
unnamed: R502.1, U501.12 (D3)
unnamed: C504.1, R505.2, R507.2, U501.5 (RCT)
unnamed: C502.1, U501.3 (RD+)
unnamed: C503.1, U501.6 (RD-)
unnamed: C501.1, R503.1, U501.4 (TCT)
unnamed: C514.1, U502.22 (1V2O)
unnamed: R509.2, U502.10 (EXRES1)
unnamed: C512.1, U502.20 (TOCAP)
unnamed: C516.2, R510.1, U502.30 (XI/CLKIN), Y501.3
unnamed: C517.1, R510.2, U502.31 (XO), Y501.1
SPE-SCK: MOD201.19 (IO15), U301.38 (SCLK)
SPE-SDI: MOD201.18 (IO14), U301.1 (SDI)
SPE-SDO: MOD201.17 (IO13), U301.2 (SDO/SPI_CFG0)
SPE-nCS: MOD201.20 (IO16), U301.29 (CS_N)
SPE-nINT: MOD201.21 (IO17), R302.1, U301.25 (INT_N)
SPE-nRST: MOD201.16 (IO12), U301.5 (RESET_N)
SPoE-1: D401.1 (K), L301.1, RV301.2
SPoE-2: D402.2 (A), L301.4, RV301.1

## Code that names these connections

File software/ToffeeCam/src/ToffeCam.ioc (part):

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Mcu.Name=STM32U575ZITx
Mcu.Package=LQFP144
Mcu.UserName=STM32U575ZITx
PA11.Mode=Device_Only
PA11.Signal=USB_OTG_FS_DM
PA12.Mode=Device_Only
PA12.Signal=USB_OTG_FS_DP
PA13\ (JTMS/SWDIO).Mode=Trace_Asynchronous_SW
PA13\ (JTMS/SWDIO).Signal=DEBUG_JTMS-SWDIO
PA14\ (JTCK/SWCLK).Mode=Trace_Asynchronous_SW
PA14\ (JTCK/SWCLK).Signal=DEBUG_JTCK-SWCLK
PA15\ (JTDI).GPIOParameters=GPIO_Label
PA15\ (JTDI).GPIO_Label=TOF_2_LPn
PA15\ (JTDI).Signal=GPIO_Output
PA2.Mode=Asynchronous
PA2.Signal=USART2_TX
PA3.Mode=Asynchronous
PA3.Signal=USART2_RX
PA4.GPIOParameters=GPIO_Label
PA4.GPIO_Label=CAM_HSYNC
PA4.Mode=Slave_8_bits_External_Synchro
PA4.Signal=DCMI_HSYNC
PA6.GPIOParameters=GPIO_Label
PA6.GPIO_Label=CAM_PCLK
PA6.Mode=Slave_8_bits_External_Synchro
PA6.Signal=DCMI_PIXCLK
PA9.Mode=Activate_VBUS
PA9.Signal=USB_OTG_FS_VBUS
PB1.GPIOParameters=GPIO_PuPd,GPIO_Label,GPIO_ModeDefaultEXTI
PB1.GPIO_Label=BUTTON
PB1.GPIO_ModeDefaultEXTI=GPIO_MODE_IT_FALLING
PB1.GPIO_PuPd=GPIO_PULLUP
PB1.Signal=GPXTI1
PB10.GPIOParameters=GPIO_Label
PB10.GPIO_Label=SPE_nRESET
PB10.Signal=GPIO_Output
PB12.GPIOParameters=GPIO_Label
PB12.GPIO_Label=TOF_1_LPn
PB12.Signal=GPIO_Output
PB13.Mode=I2C
PB13.Signal=I2C2_SCL
PB14.Mode=I2C
PB14.Signal=I2C2_SDA
PB3\ (JTDO/TRACESWO).Mode=Trace_Asynchronous_SW
PB3\ (JTDO/TRACESWO).Signal=DEBUG_JTDO-SWO
PB4\ (NJTRST).GPIOParameters=GPIO_Label
PB4\ (NJTRST).GPIO_Label=TOF_5_LPn
PB4\ (NJTRST).Signal=GPIO_Output
PB5.GPIOParameters=GPIO_Label
PB5.GPIO_Label=MCU-STATUS-2
PB5.Signal=GPIO_Output
PB6.GPIOParameters=GPIO_Label
PB6.GPIO_Label=CAM_D5
PB6.Mode=Slave_8_bits_External_Synchro
PB6.Signal=DCMI_D5
PB7.GPIOParameters=GPIO_Label
PB7.GPIO_Label=CAM_VSYNC
PB7.Mode=Slave_8_bits_External_Synchro
PB7.Signal=DCMI_VSYNC
PB8.GPIOParameters=GPIO_Label
PB8.GPIO_Label=TOF_7_LPn
PB8.Signal=GPIO_Output
PB9.GPIOParameters=GPIO_Label
PB9.GPIO_Label=CAM_XCLK
PB9.Signal=S_TIM4_CH4
PC0.GPIOParameters=GPIO_Label
PC0.GPIO_Label=CAM_I2C_SCL
PC0.Mode=I2C
PC0.Signal=I2C3_SCL
PC1.GPIOParameters=GPIO_Label
PC1.GPIO_Label=CAM_I2C_SDA
PC1.Mode=I2C
PC1.Signal=I2C3_SDA
PC10.GPIOParameters=GPIO_Label
PC10.GPIO_Label=TOF_3_LPn
PC10.Signal=GPIO_Output
PC11.GPIOParameters=GPIO_Label
PC11.GPIO_Label=TOF_4_LPn
PC11.Signal=GPIO_Output
PC12.GPIOParameters=GPIO_Label
PC12.GPIO_Label=TOF_nPWDN
PC12.Signal=GPIO_Output
PC3.GPIOParameters=GPIO_PuPd,GPIO_Label,GPIO_ModeDefaultOutputPP
PC3.GPIO_Label=CAM_nRESET
PC3.GPIO_ModeDefaultOutputPP=GPIO_MODE_OUTPUT_OD
PC3.GPIO_PuPd=GPIO_NOPULL
PC3.Signal=GPIO_Output
PC4.GPIOParameters=GPIO_PuPd,GPIO_Label
PC4.GPIO_Label=ETH_MEDIA_SELECT
PC4.GPIO_PuPd=GPIO_PULLUP
PC4.Signal=GPIO_Output
PC6.GPIOParameters=GPIO_Label
PC6.GPIO_Label=CAM_D0
PC6.Mode=Slave_8_bits_External_Synchro
PC6.Signal=DCMI_D0
PC7.GPIOParameters=GPIO_Label
PC7.GPIO_Label=CAM_D1
PC7.Mode=Slave_8_bits_External_Synchro
PC7.Signal=DCMI_D1
PD0.GPIOParameters=GPIO_Label
PD0.GPIO_Label=ETH_BUS_D2
PD0.Signal=FMC_D2_DA2
PD1.GPIOParameters=GPIO_Label
PD1.GPIO_Label=ETH_BUS_D3
PD1.Signal=FMC_D3_DA3
PD11.GPIOParameters=GPIO_Label
PD11.GPIO_Label=TOF_I2C1_RST
PD11.Signal=GPIO_Output
PD12.Mode=I2C
PD12.Signal=I2C4_SCL
PD13.Mode=I2C
PD13.Signal=I2C4_SDA
PD14.GPIOParameters=GPIO_Label
PD14.GPIO_Label=ETH_BUS_D0
PD14.Signal=FMC_D0_DA0
PD15.GPIOParameters=GPIO_Label
PD15.GPIO_Label=ETH_BUS_D1
PD15.Signal=FMC_D1_DA1
PD4.GPIOParameters=GPIO_Label
PD4.GPIO_Label=ETH_BUS_nRD
PD4.Signal=FMC_NOE
PD5.GPIOParameters=GPIO_Label
PD5.GPIO_Label=ETH_BUS_nWR
PD5.Signal=FMC_NWE
PD7.GPIOParameters=GPIO_Label
PD7.GPIO_Label=ETH_BUS_nCS
PD7.Mode=NorPsramChipSelect1_1
PD7.Signal=FMC_NE1
PE0.GPIOParameters=GPIO_Label
PE0.GPIO_Label=CAM_D2
PE0.Mode=Slave_8_bits_External_Synchro
PE0.Signal=DCMI_D2
PE1.GPIOParameters=GPIO_Label
PE1.GPIO_Label=CAM_D3
PE1.Mode=Slave_8_bits_External_Synchro
PE1.Signal=DCMI_D3
PE10.GPIOParameters=GPIO_Label
PE10.GPIO_Label=ETH_BUS_D7
PE10.Signal=FMC_D7_DA7
PE13.GPIOParameters=GPIO_Label
PE13.GPIO_Label=SPE_SPI1_SCK
PE13.Mode=Full_Duplex_Master
PE13.Signal=SPI1_SCK
PE14.GPIOParameters=GPIO_Label
PE14.GPIO_Label=SPE_SPI1_MISO
PE14.Mode=Full_Duplex_Master
PE14.Signal=SPI1_MISO
PE15.GPIOParameters=GPIO_Label
PE15.GPIO_Label=SPE_SPI1_MOSI
PE15.Mode=Full_Duplex_Master
PE15.Signal=SPI1_MOSI
PE2.GPIOParameters=GPIO_Label
PE2.GPIO_Label=ETH_BUS_nRST
PE2.Signal=GPIO_Output
PE3.GPIOParameters=GPIO_Label
PE3.GPIO_Label=ETH_BUS_nINT
PE3.Signal=GPXTI3
PE4.GPIOParameters=GPIO_Label
PE4.GPIO_Label=CAM_D4
PE4.Mode=Slave_8_bits_External_Synchro
PE4.Signal=DCMI_D4
PE5.GPIOParameters=GPIO_Label
PE5.GPIO_Label=CAM_D6
PE5.Mode=Slave_8_bits_External_Synchro
PE5.Signal=DCMI_D6
PE6.GPIOParameters=GPIO_Label
PE6.GPIO_Label=CAM_D7
PE6.Mode=Slave_8_bits_External_Synchro
PE6.Signal=DCMI_D7
PE7.GPIOParameters=GPIO_Label
PE7.GPIO_Label=ETH_BUS_D4
PE7.Signal=FMC_D4_DA4
PE8.GPIOParameters=GPIO_Label
PE8.GPIO_Label=ETH_BUS_D5
PE8.Signal=FMC_D5_DA5
PE9.GPIOParameters=GPIO_Label
PE9.GPIO_Label=ETH_BUS_D6
PE9.Signal=FMC_D6_DA6
PF0.Signal=FMC_A0
PF1.Signal=FMC_A1
PF10.GPIOParameters=GPIO_Label
PF10.GPIO_Label=DUMMY5
PF10.Signal=GPIO_Output
PF12.Signal=FMC_A6
PF13.Signal=FMC_A7
PF14.Signal=FMC_A8
PF15.Signal=FMC_A9
PF2.Signal=FMC_A2
PF3.Signal=FMC_A3
PF4.Signal=FMC_A4
PF5.Signal=FMC_A5
PF6.GPIOParameters=GPIO_Label
PF6.GPIO_Label=DUMMY1
PF6.Signal=GPIO_Output
PF7.GPIOParameters=GPIO_Label
PF7.GPIO_Label=DUMMY2
PF7.Signal=GPIO_Output
PF8.GPIOParameters=GPIO_Label
PF8.GPIO_Label=DUMMY3
PF8.Signal=GPIO_Output
PF9.GPIOParameters=GPIO_Label
PF9.GPIO_Label=DUMMY4
PF9.Signal=GPIO_Output
PG12.GPIOParameters=GPIO_Label
PG12.GPIO_Label=TOF_I2C2_RST
PG12.Signal=GPIO_Output
PG13.Mode=I2C
PG13.Signal=I2C1_SDA
PG14.Mode=I2C
PG14.Signal=I2C1_SCL
PG3.GPIOParameters=GPIO_Label
PG3.GPIO_Label=MCU_STATUS_1
PG3.Signal=GPIO_Output
PH0-OSC_IN\ (PH0).Mode=HSE-External-Oscillator
PH0-OSC_IN\ (PH0).Signal=RCC_OSC_IN
PH1-OSC_OUT\ (PH1).Mode=HSE-External-Oscillator
PH1-OSC_OUT\ (PH1).Signal=RCC_OSC_OUT
PH3-BOOT0.GPIOParameters=GPIO_Label
PH3-BOOT0.GPIO_Label=TOF_6_LPn
PH3-BOOT0.Signal=GPIO_Output
RCC.HSE_VALUE=16000000
RCC.SYSCLKFreq_VALUE=96000000
RCC.SYSCLKSource=RCC_SYSCLKSOURCE_PLLCLK
board=custom

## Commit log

2023-08-10 Second hardware prototype
2023-08-10 Initial software
2023-08-12 Clean schematics
2023-08-13 Add drawings
2023-08-16 Add docs
2023-08-17 Docs up to date
2023-08-20 Docs for Wiznet's contest
2023-08-28 Add FreeRTOS
2023-08-29 Cube sttings
2023-08-29 Move project to Clion C++ project
2023-09-03 Wiznet Demo App as FreeRTOS task
